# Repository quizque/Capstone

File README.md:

# Stargazer Flight Logger
## Capstone 2024

### Summery

Stargazer is an all-in-one logger capable of high-speed data saving and transmitting of high-altitude rocket flights. It is one IO pin away from a full flight computer that is capable of controlling ignition charges and performing TVC. Stargazer contains an IMU (gyroscope/accelerometer), high-g accelerometer, barometer, magnetometer, and GPS. All of these sensors combine together allow for the calculation of direction, trajectory, orientation, etc. which can potentially allow for real-time correction.

### Directory Setup

**sensor-testing/**

Contains programs and results from various sensor tests.

**stargazer/**
 
Contains KiCAD project for Stargazer

**stargazer-demo-src/**

Contains firmware for the Stargazer demo

**stargazer-src/**

Contains the main firmware for Stargazer

**tools/**

Contains the script to convert raw data obtained from Stargazer into a CSV file. Also contains the demo day visualizers

**vibration-bay-src/**

Contains the firmware used in the vibration testing bay

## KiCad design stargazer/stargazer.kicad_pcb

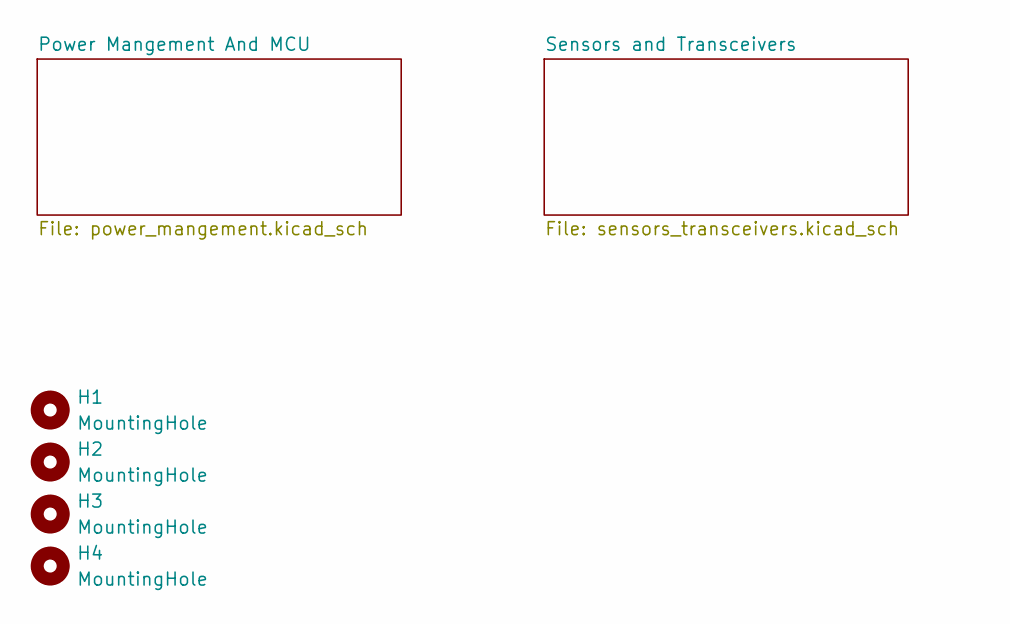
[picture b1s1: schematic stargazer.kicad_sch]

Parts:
H1, H2, H3, H4: MountingHole; MountingHole_3.2mm_M3_DIN965_Pad

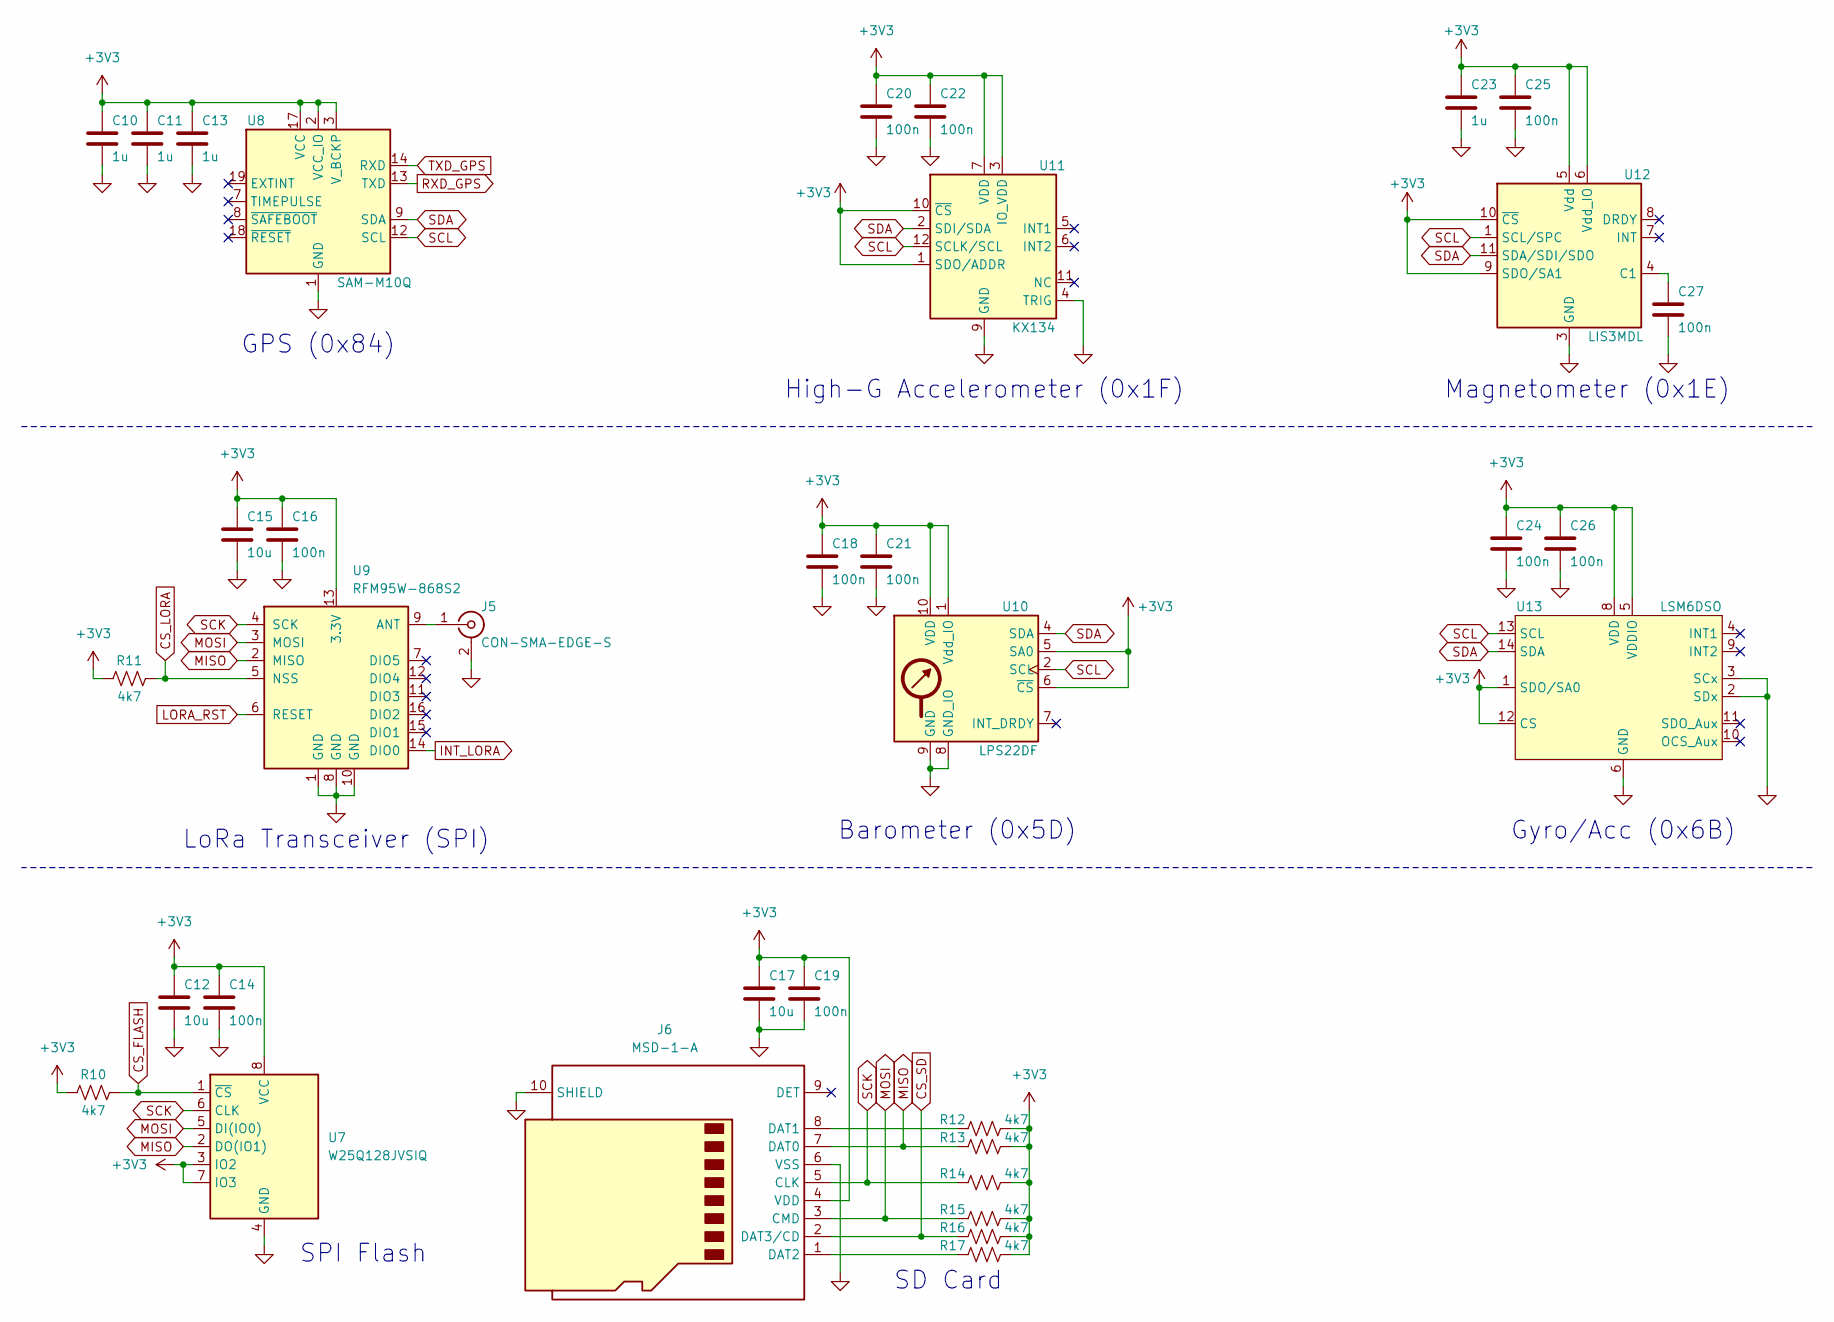
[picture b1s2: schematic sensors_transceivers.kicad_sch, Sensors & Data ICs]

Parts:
C10, C11, C13, C23: 1u; C_0603_1608Metric; digikeynumber CL10B105KP8NFNC
C12, C15, C17: 10u; C_0603_1608Metric; digikeynumber CL10A106KQ8NNNC
C14, C16, C18, C19, C20, C21, C22, C24, C25, C26, C27: 100n; C_0603_1608Metric; digikeynumber CL10B104KO8NNWC
J5: CON-SMA-EDGE-S; RFSOLUTIONS_CON-SMA-EDGE-S; digikeynumber CON-SMA-EDGE-S
J6: MSD-1-A; CONN9_MSD-1_CUD; digikeynumber MSD-1-A
R10, R11, R12, R13, R14, R15, R16, R17: 4k7; R_0603_1608Metric; digikeynumber RC0603FR-074K7L
U7: W25Q128JVSIQ; SOIC-8_5.23x5.23mm_P1.27mm; digikeynumber W25Q128JVSIQ
U8: SAM-M10Q; ublox_SAM-M10Q; digikeynumber SAM-M10Q-00B
U9: RFM95W-868S2; HOPERF_RFM9XW_SMD
U10: LPS22DF; ST_HLGA-10_2x2mm_P0.5mm_LayoutBorder3x2y; digikeynumber LPS22DFTR
U11: KX134; LGA-12_2x2mm_P0.5mm; digikeynumber KX134-1211
U12: LIS3MDL; LGA-12_2x2mm_P0.5mm; digikeynumber LIS3MDLTR
U13: LSM6DSO; LGA-14_3x2.5mm_P0.5mm_LayoutBorder3x4y; digikeynumber LSM6DSOTR

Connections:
+3V3: C10.1, C11.1, C12.1, C13.1, C14.1, C15.1, C16.1, C17.1, C18.1, C19.1, C20.1, C21.1, C22.1, C23.1, C24.1, C25.1, C26.1, J6.4 (VDD), R10.1, R11.1, R12.2, R13.2, R14.2, R15.2, R16.2, R17.2, U7.3 (IO2), U7.7 (IO3), U7.8 (VCC), U8.2 (VCC_IO), U8.3 (V_BCKP), U8.17 (VCC), U9.13 (3.3V), U10.1 (Vdd_IO), U10.5 (SA0), U10.6 (~CS), U10.10 (VDD), U11.1 (SDO/ADDR), U11.3 (IO_VDD), U11.7 (VDD), U11.10 (~CS), U12.5 (Vdd), U12.6 (Vdd_IO), U12.9 (SDO/SA1), U12.10 (~CS), U13.1 (SDO/SA0), U13.5 (VDDIO), U13.8 (VDD), U13.12 (CS); also elsewhere on the board
CS_FLASH: R10.2, U7.1 (~CS); also elsewhere on the board
CS_LORA: R11.2, U9.5 (NSS); also elsewhere on the board
CS_SD: J6.2 (DAT3/CD), R16.1; also elsewhere on the board
GND: C10.2, C11.2, C12.2, C13.2, C14.2, C15.2, C16.2, C17.2, C18.2, C19.2, C20.2, C21.2, C22.2, C23.2, C24.2, C25.2, C26.2, C27.2, J5.2 (Ext), J6.6 (VSS), J6.10 (SHIELD), U7.4 (GND), U8.1 (GND), U8.4 (GND), U8.5 (GND), U8.6 (GND), U8.10 (GND), U8.11 (GND), U8.15 (GND), U8.16 (GND), U8.20 (GND), U9.1 (GND), U9.8 (GND), U9.10 (GND), U10.3 (GND), U10.8 (GND_IO), U10.9 (GND), U11.4 (TRIG), U11.8 (GND), U11.9 (GND), U12.2 (GND), U12.3 (GND), U12.12 (GND), U13.2 (SDx), U13.3 (SCx), U13.6 (GND), U13.7 (GND); also elsewhere on the board
INT_LORA: U9.14 (DIO0); also elsewhere on the board
LORA_RST: U9.6 (RESET); also elsewhere on the board
MISO: J6.7 (DAT0), R13.1, U7.2 (DO(IO1)), U9.2 (MISO); also elsewhere on the board
MOSI: J6.3 (CMD), R15.1, U7.5 (DI(IO0)), U9.3 (MOSI); also elsewhere on the board
unnamed: J5.1 (In), U9.9 (ANT)
unnamed: J6.8 (DAT1), R12.1
unnamed: J6.1 (DAT2), R17.1
unnamed: C27.1, U12.4 (C1)
RXD_GPS: U8.13 (TXD); also elsewhere on the board
SCK: J6.5 (CLK), R14.1, U7.6 (CLK), U9.4 (SCK); also elsewhere on the board
SCL: U8.12 (SCL), U10.2 (SCL), U11.12 (SCLK/SCL), U12.1 (SCL/SPC), U13.13 (SCL); also elsewhere on the board
SDA: U8.9 (SDA), U10.4 (SDA), U11.2 (SDI/SDA), U12.11 (SDA/SDI/SDO), U13.14 (SDA); also elsewhere on the board
TXD_GPS: U8.14 (RXD); also elsewhere on the board

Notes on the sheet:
Magnetometer (0x1E)
GPS (0x84)
High-G Accelerometer (0x1F)
SD Card
Gyro/Acc (0x6B)
LoRa Transceiver (SPI)
SPI Flash
Barometer (0x5D)

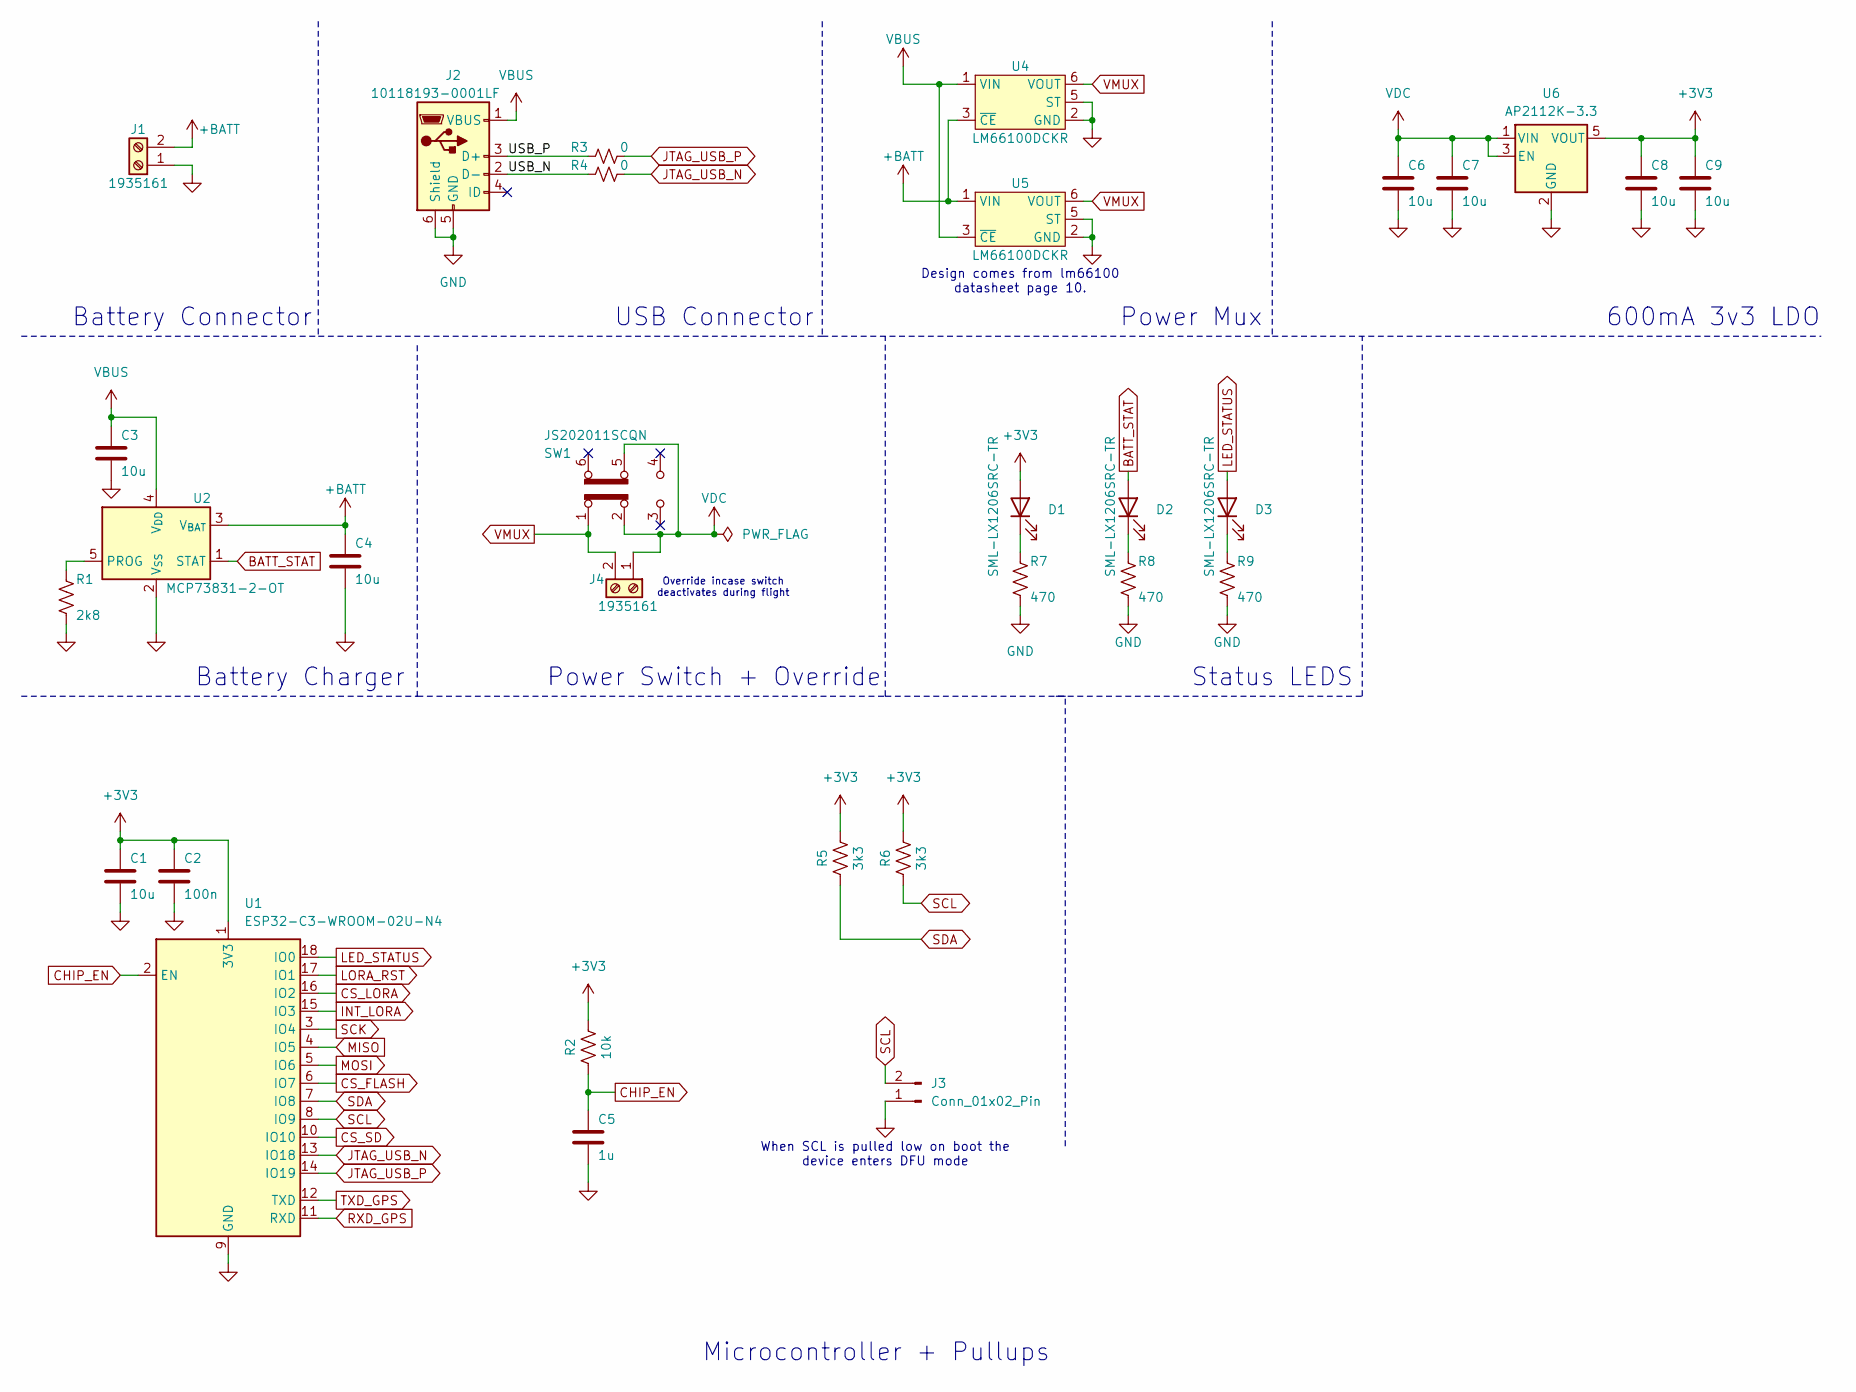
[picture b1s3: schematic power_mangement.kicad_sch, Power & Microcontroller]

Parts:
C1, C3, C4, C6, C7, C8, C9: 10u; C_0603_1608Metric; digikeynumber CL10A106KQ8NNNC
C2: 100n; C_0603_1608Metric; digikeynumber CL10B104KO8NNWC
C5: 1u; C_0603_1608Metric; digikeynumber CL10B105KP8NFNC
D1, D2, D3: SML-LX1206SRC-TR; LED_0805_2012Metric; digikeynumber SML-LX1206SRC-TR
J1, J4: 1935161; PHOENIX_1935161; digikeynumber 1935161
J2: 10118193-0001LF; AMPHENOL_10118193-0001LF; digikeynumber 10118193-0001LF
J3: Conn_01x02_Pin; PinSocket_1x02_P2.54mm_Vertical
R1: 2k8; R_0603_1608Metric; digikeynumber RC0603DR-072K8L
R2: 10k; R_0603_1608Metric; digikeynumber RC0603DR-0710KL
R3, R4: 0; R_0603_1608Metric; digikeynumber RC0603FR-130RL
R5, R6: 3k3; R_0603_1608Metric; digikeynumber RC0603FR-103K3L
R7, R8, R9: 470; R_0603_1608Metric; digikeynumber RC0603FR-13470RL
SW1: JS202011SCQN; SW_JS202011SCQN; digikeynumber JS202011SCQN
U1: ESP32-C3-WROOM-02U-N4; ESP32-C3-WROOM-02U; digikeynumber ESP32-C3-WROOM-02U-N4
U2: MCP73831-2-OT; SOT-23-5; digikeynumber MCP73831T-2ACI/OT
U4, U5: LM66100DCKR; DCK6_TEX; digikeynumber LM66100DCKR
U6: AP2112K-3.3; SOT-23-5; digikeynumber AP2112K-3.3TRG1

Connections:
+3V3: C1.1, C2.1, C8.1, C9.1, D1.2 (A), R2.2, R5.2, R6.2, U1.1 (3V3), U6.5 (VOUT); also elsewhere on the board
+BATT: C4.1, J1.2, U2.3 (V_{BAT}), U4.3 (~CE), U5.1 (VIN)
/Power Mangement And MCU/USB_N: J2.2 (D-), R4.1
/Power Mangement And MCU/USB_P: J2.3 (D+), R3.1
BATT_STAT: D2.2 (A), U2.1 (STAT)
CHIP_EN: C5.1, R2.1, U1.2 (EN)
CS_FLASH: U1.6 (IO7); also elsewhere on the board
CS_LORA: U1.16 (IO2); also elsewhere on the board
CS_SD: U1.10 (IO10); also elsewhere on the board
GND: C1.2, C2.2, C3.2, C4.2, C5.2, C6.2, C7.2, C8.2, C9.2, J1.1, J2.5 (GND), J2.6 (Shield), J3.1, R1.2, R7.2, R8.2, R9.2, U1.9 (GND), U1.19 (GND), U2.2 (V_{SS}), U4.2 (GND), U4.5 (ST), U5.2 (GND), U5.5 (ST), U6.2 (GND); also elsewhere on the board
INT_LORA: U1.15 (IO3); also elsewhere on the board
JTAG_USB_N: R4.2, U1.13 (IO18)
JTAG_USB_P: R3.2, U1.14 (IO19)
LED_STATUS: D3.2 (A), U1.18 (IO0)
LORA_RST: U1.17 (IO1); also elsewhere on the board
MISO: U1.4 (IO5); also elsewhere on the board
MOSI: U1.5 (IO6); also elsewhere on the board
unnamed: D1.1 (K), R7.1
unnamed: D2.1 (K), R8.1
unnamed: D3.1 (K), R9.1
unnamed: R1.1, U2.5 (PROG)
RXD_GPS: U1.11 (RXD); also elsewhere on the board
SCK: U1.3 (IO4); also elsewhere on the board
SCL: J3.2, R6.1, U1.8 (IO9); also elsewhere on the board
SDA: R5.1, U1.7 (IO8); also elsewhere on the board
TXD_GPS: U1.12 (TXD); also elsewhere on the board
VBUS: C3.1, J2.1 (VBUS), U2.4 (V_{DD}), U4.1 (VIN), U5.3 (~CE)
VDC: C6.1, C7.1, J4.1, SW1.2 (B), SW1.5 (B), U6.1 (VIN), U6.3 (EN)
VMUX: J4.2, SW1.1 (A), U4.6 (VOUT), U5.6 (VOUT)

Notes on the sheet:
600mA 3v3 LDO
USB Connector
Battery Charger
Power Switch + Override
Design comes from lm66100 datasheet page 10.
Power Mux
When SCL is pulled low on boot the device enters DFU mode
Status LEDS
Override incase switch deactivates during flight
Microcontroller + Pullups
Battery Connector

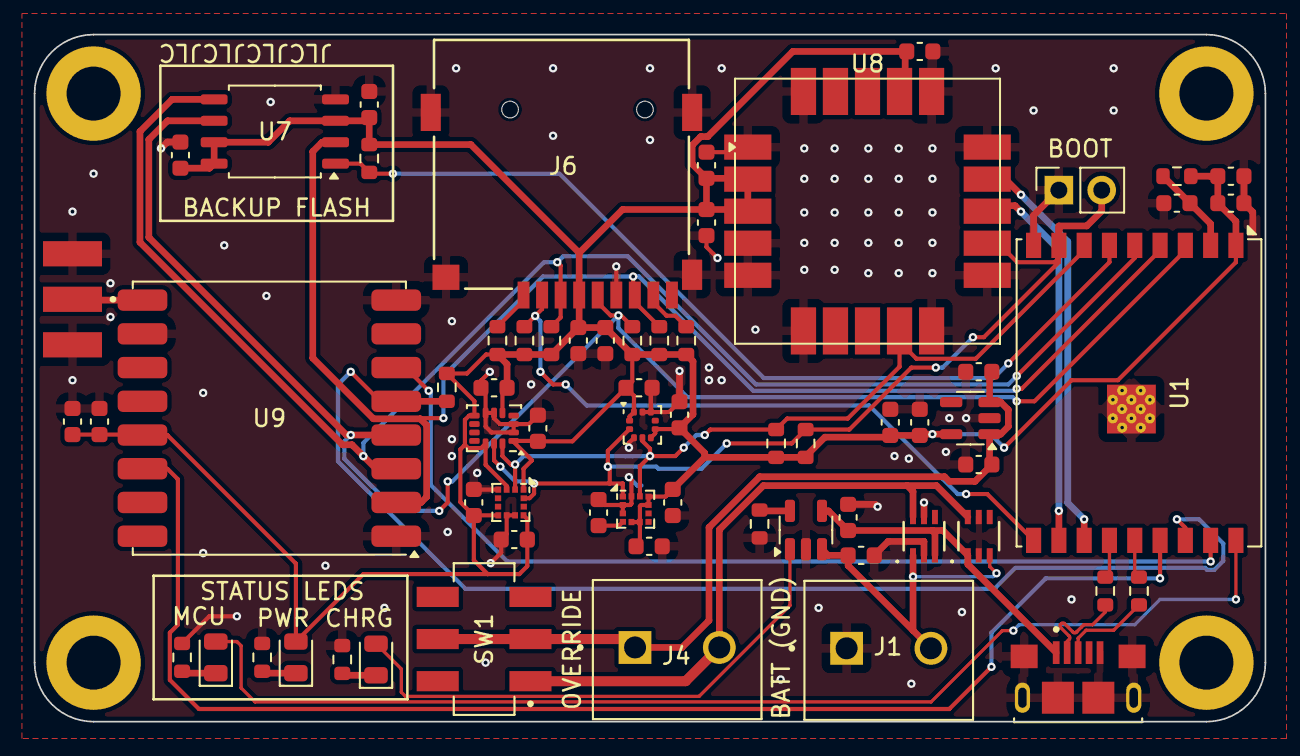
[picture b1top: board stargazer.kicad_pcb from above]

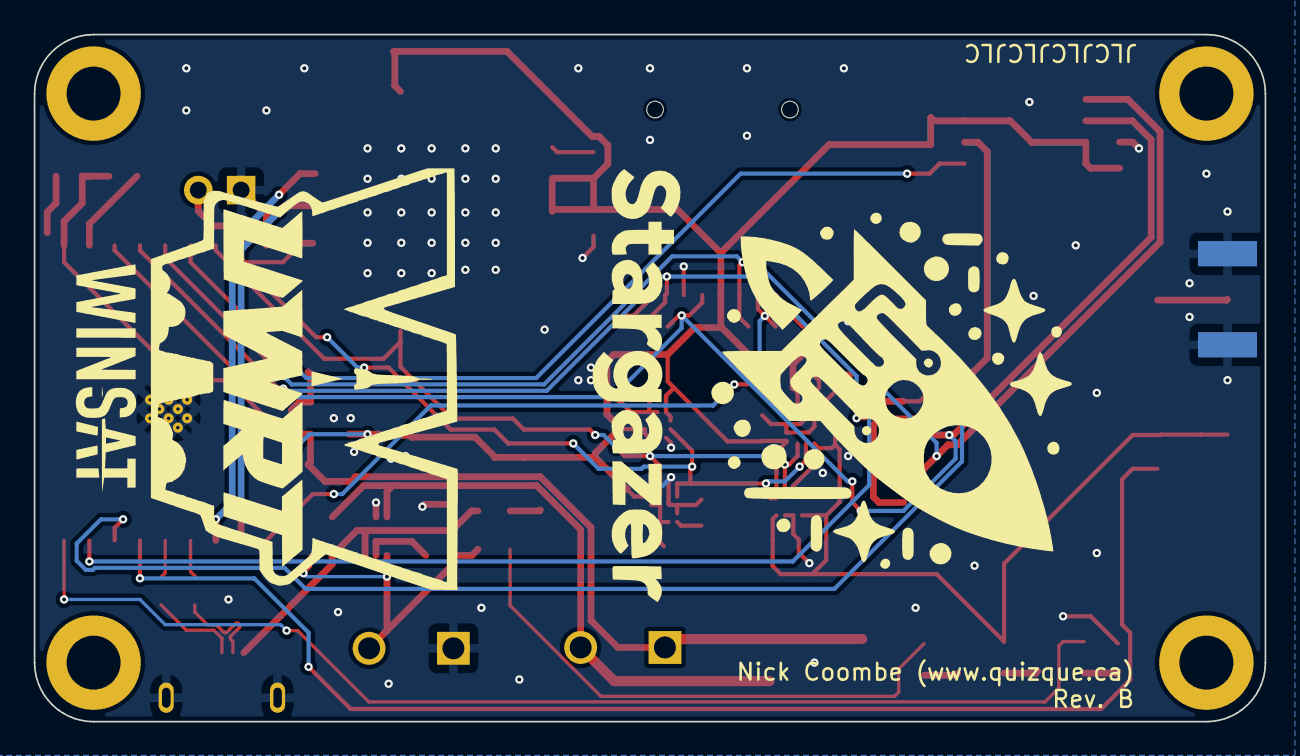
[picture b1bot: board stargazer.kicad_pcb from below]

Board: 2 copper layers, 73.0 x 40.8 mm, 72 parts (2 on the bottom side), 33 nets.

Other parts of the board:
logo: LOGO
winsatlogo: LOGO

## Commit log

2024-02-12 Added asteroid (transmitter)
2024-02-26 Added micropython test scripts
2024-03-05 Added SX1262 module stuff
2024-03-19 Updated Comet
2024-04-03 Added stargazer
2024-04-05 Added more sensors
2024-04-09 Almost done stargazer
2024-05-11 Moved to misc
2024-05-12 New Layout
2024-05-14 Prerouting
2024-05-15 Revision 1
2024-05-15 Cleaned files
2024-05-22 Added source code
2024-05-23 Board Rev B WIP
2024-05-23 Working source code
2024-05-23 Working GPS + UART USB
2024-05-23 Rev B schem finished
2024-05-24 Revision B
2024-05-24 calibrated mag
2024-05-29 Added model rocket sim
2024-06-04 Working device tester
2024-06-09 Added more logging
2024-06-09 More logging
2024-06-10 ROCKET LAUNCHED!!!!
2024-06-27 rocket launch data
2024-06-27 Switch to USLetter paper for printing
2024-07-02 working ahrs
2024-07-23 Added visualisers
2024-07-23 Improved AHRS
2024-07-26 Added rest of demo
2024-07-26 Properly clear screen for OpenGL
2024-07-26 Stargazer PCB print update
2024-07-28 Redundancy mod
2024-07-28 Code cleanup + Documentation
2024-07-28 Renamed demo code
2024-07-29 Consolidating branches
2024-07-29 More code cleanup
2024-07-29 Repo cleanup
2024-07-31 Added vibration bay firmware
2024-07-31 Cleaned repo and added rocket model
